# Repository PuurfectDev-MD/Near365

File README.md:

# Wacky and cute- *self claimed :)* Music Player 

**Music Player v1** is a interactive  media device (media form: music, voice recording, text, gifs and video possibly) powered by an ESP32-S3.I designed it as a personalized gift,to play unique music, affirmations,  every single day onpre-programmed schedule. v2 will have an APi endpoint to post voice recordings over the internet and other cool features. The device is a complete package for audio related projects and can be modified into other creative ideas like - (voice journal keeper, online music streaming and many more!)

---

## Features

* **Daily Present:** Automatically fetches unique content (music and text(affiramtions/notes)) from an SD card based on the current date.
* **High-quality Audio:** Uses I2S protocol with a MAX98357A DAC for clear, non-blocking WAV file playback.
* **Voice Recorder:** Record and save voice memos directly to the SD card for future playback ** Plans to stream it over the internet
* **Music Player:** Plays music playlists from the sd card
* **Peculiar Cute design** Cute 3d model case enclosure with a tounge sticking out 😛

---

##  Hardware Design

### Schematic
The system integrates an ESP32-S3 with I2S audio, SPI SD card communication, and I2C/SPI display interfacing.

### PCB Design
A custom 2-layer PCB design from kicad.

### Power Board

### 3D Model for Case
A custom 3d model case from fusion 360

---
##  Bill of Materials (BOM)

| Component           | Description                                  | Quantity |
| :------------------ | :------------------------------------------- | :------- |
| **Microcontroller** | ESP32-S3 (WROOM-1-N16R8)                     | 1        |
| **Display** | 2.4" TFT LCD (ILI9341 Driver)                | 1        |
| **Audio DAC/Amp** | MAX98357A I2S Class D Amplifier              | 1        |
| **Speaker** | 3W 4-Ohm Internal Speaker                    | 1        |
| **Rotary Encoder** | EC11 Encoder with Push-Button Switch         | 1        |
| **Touch Sensor** | TTP223 Capacitive Touch Module (Soft Power)  | 1        |
| **SD card module** | Adafruit Micro SD Card Breakout Board      | 1        |
| **Microphone** | INMP441 I2S Digital Omnidirectional Mic      | 1        |
| **RTC Module** | DS3231 High-Precision I2C RTC                | 1        |
| **Storage Card** | 16GB Micro SD Card       | 1        |
| **BMS Board** | Custom made battery management system      | 1        |
> [!NOTE]
> This is just a summary of the BOM. The complete BOM can be found in [`/BOM details/project.csv`](BOM%20details/project.csv)
---

##  Project Structure

* `firmware/pages`: Contains the class logic for each UI state (`Daily`, `Music`, `Record`, `History`).
* `main.py`: The primary async loop and state machine handler.
* `setup.py`: Hardware initialization and pin mapping.
* `master.json`: The central database for the daily gift schedule.

## File Structure:

* `/3d Model`: Contains fusion and 3d printing files for the case.
* `/firmware`: Contains the code
* `Kicad`: Kicad files (both power and main board)
       * `Power_kicad`: Custom made bms system kicad project
       * `main_kicad`: main pcb kicad project
* `/images`: For images of README.md
* `/BOM details`: For BOM from Kicad and my cost compiled for the enitre project
          *`project.csv`: For cost compiled BOM
* `Gerber Files`: For JLCPCB or any other manufacturer
          * `production_main`: Gerber for the main pcb
          * `production_power`: Gerber for the BMS pcb

---

# Why build this?
I built it becasue I really wanted to get into making a custom esp32 chip board and happened to stumble upon a music player gift idea. And from there I spiralled into making the best version of my idea. It plays a different song and displays unique affiramtions from a predefined library to bringten up someones day. OFC my handcrafted playlist library is the biggest treasure :). You can build your own too! For yourself or for someone else. Good Luck >> After you complete it, share it with me from the info at https://manishd.is-a.dev/ .

# My build

### What Works Perfectly:
* **Playback:** Successfully fetches scheduled daily gifts/affirmations and plays audio
* **Network & Time Sync:** Connects to the internet to update and synchronize time data via API
* **Custom UI:** The custom LVGL-based TFT user interface turned out beautifully and performs well 

### Improvements that could better my build:
1. **The BMS Architecture:** Looking back, splitting the power/BMS circuit onto a separate board added unnecessary assembly complexity. For v2, the power management circuit will on a singl PCB.
2. **I2S Audio Recording:** While standalone microphone test scripts work flawlessly, fully integrating the voice-recording firmware into the main async package remains a work-in-progress becasue of some pin conflict
3. **Prototyping Materials Matter:** Using standard breadboard jumper wires and low-quality solder wire made internal routing extremely messy and prone to weak joints and gave me a veryvery hard time during building. This also made the final result messy and prone to breaking down/short ciruit.
4. **Hardware Casualty:** During the final hardware assembly stages, the TFT display took some physical damage which was just devestating. But it works kinda alright so fine i guess.

<details>
<summary><b> This is the tft after damage</b></summary>
<br />
<p align="center">
  
  <br />
  <sub>It works though so its fine guess.</sub>
</p>
</details>

---
> 💡 **Note:** This video was recorded during early testing. Some UI components shown in the gallery below are not visible in the clip. use the static images for final UI reference.

#### From the outside
<table width="100%">
  <tr>
    <td width="50%" align="center">
      
      <br />
      <sub><b>Enclosure Assembly</b></sub>
    </td>
    <td width="50%" align="center">
      
      <br />
      <sub><b>Wacky Cute Tongue Profile 😛</b></sub>
    </td>
  </tr>
</table>

#### UI
<table width="100%">
  <tr>
    <td width="33%" align="center">
      
      <br />
      <sub><b>Home</b></sub>
    </td>
    <td width="33%" align="center">
      
      <br />
      <sub><b>Music Screen</b></sub>
    </td>
    <td width="33%" align="center">
      
      <br />
      <sub><b>Gift screen</b></sub>
    </td>
  </tr>
</table>

## AI USE:
I used AI heavily for the coding part. Around 40%-50%. Majority of the project is hardware based so AI use for the whole project is less than 25%. The things I used AI for - 

- Help with KICAD DRC issue
- Help with hole configuration on Fusion 360
- Troubleshooting design elements
- LVGL library and firmware setup (first time using it so thats why)
- LVGL library functions
- Acurate Encoder Input 

And a lot of debugging stuff.

*Created with love❤️.*

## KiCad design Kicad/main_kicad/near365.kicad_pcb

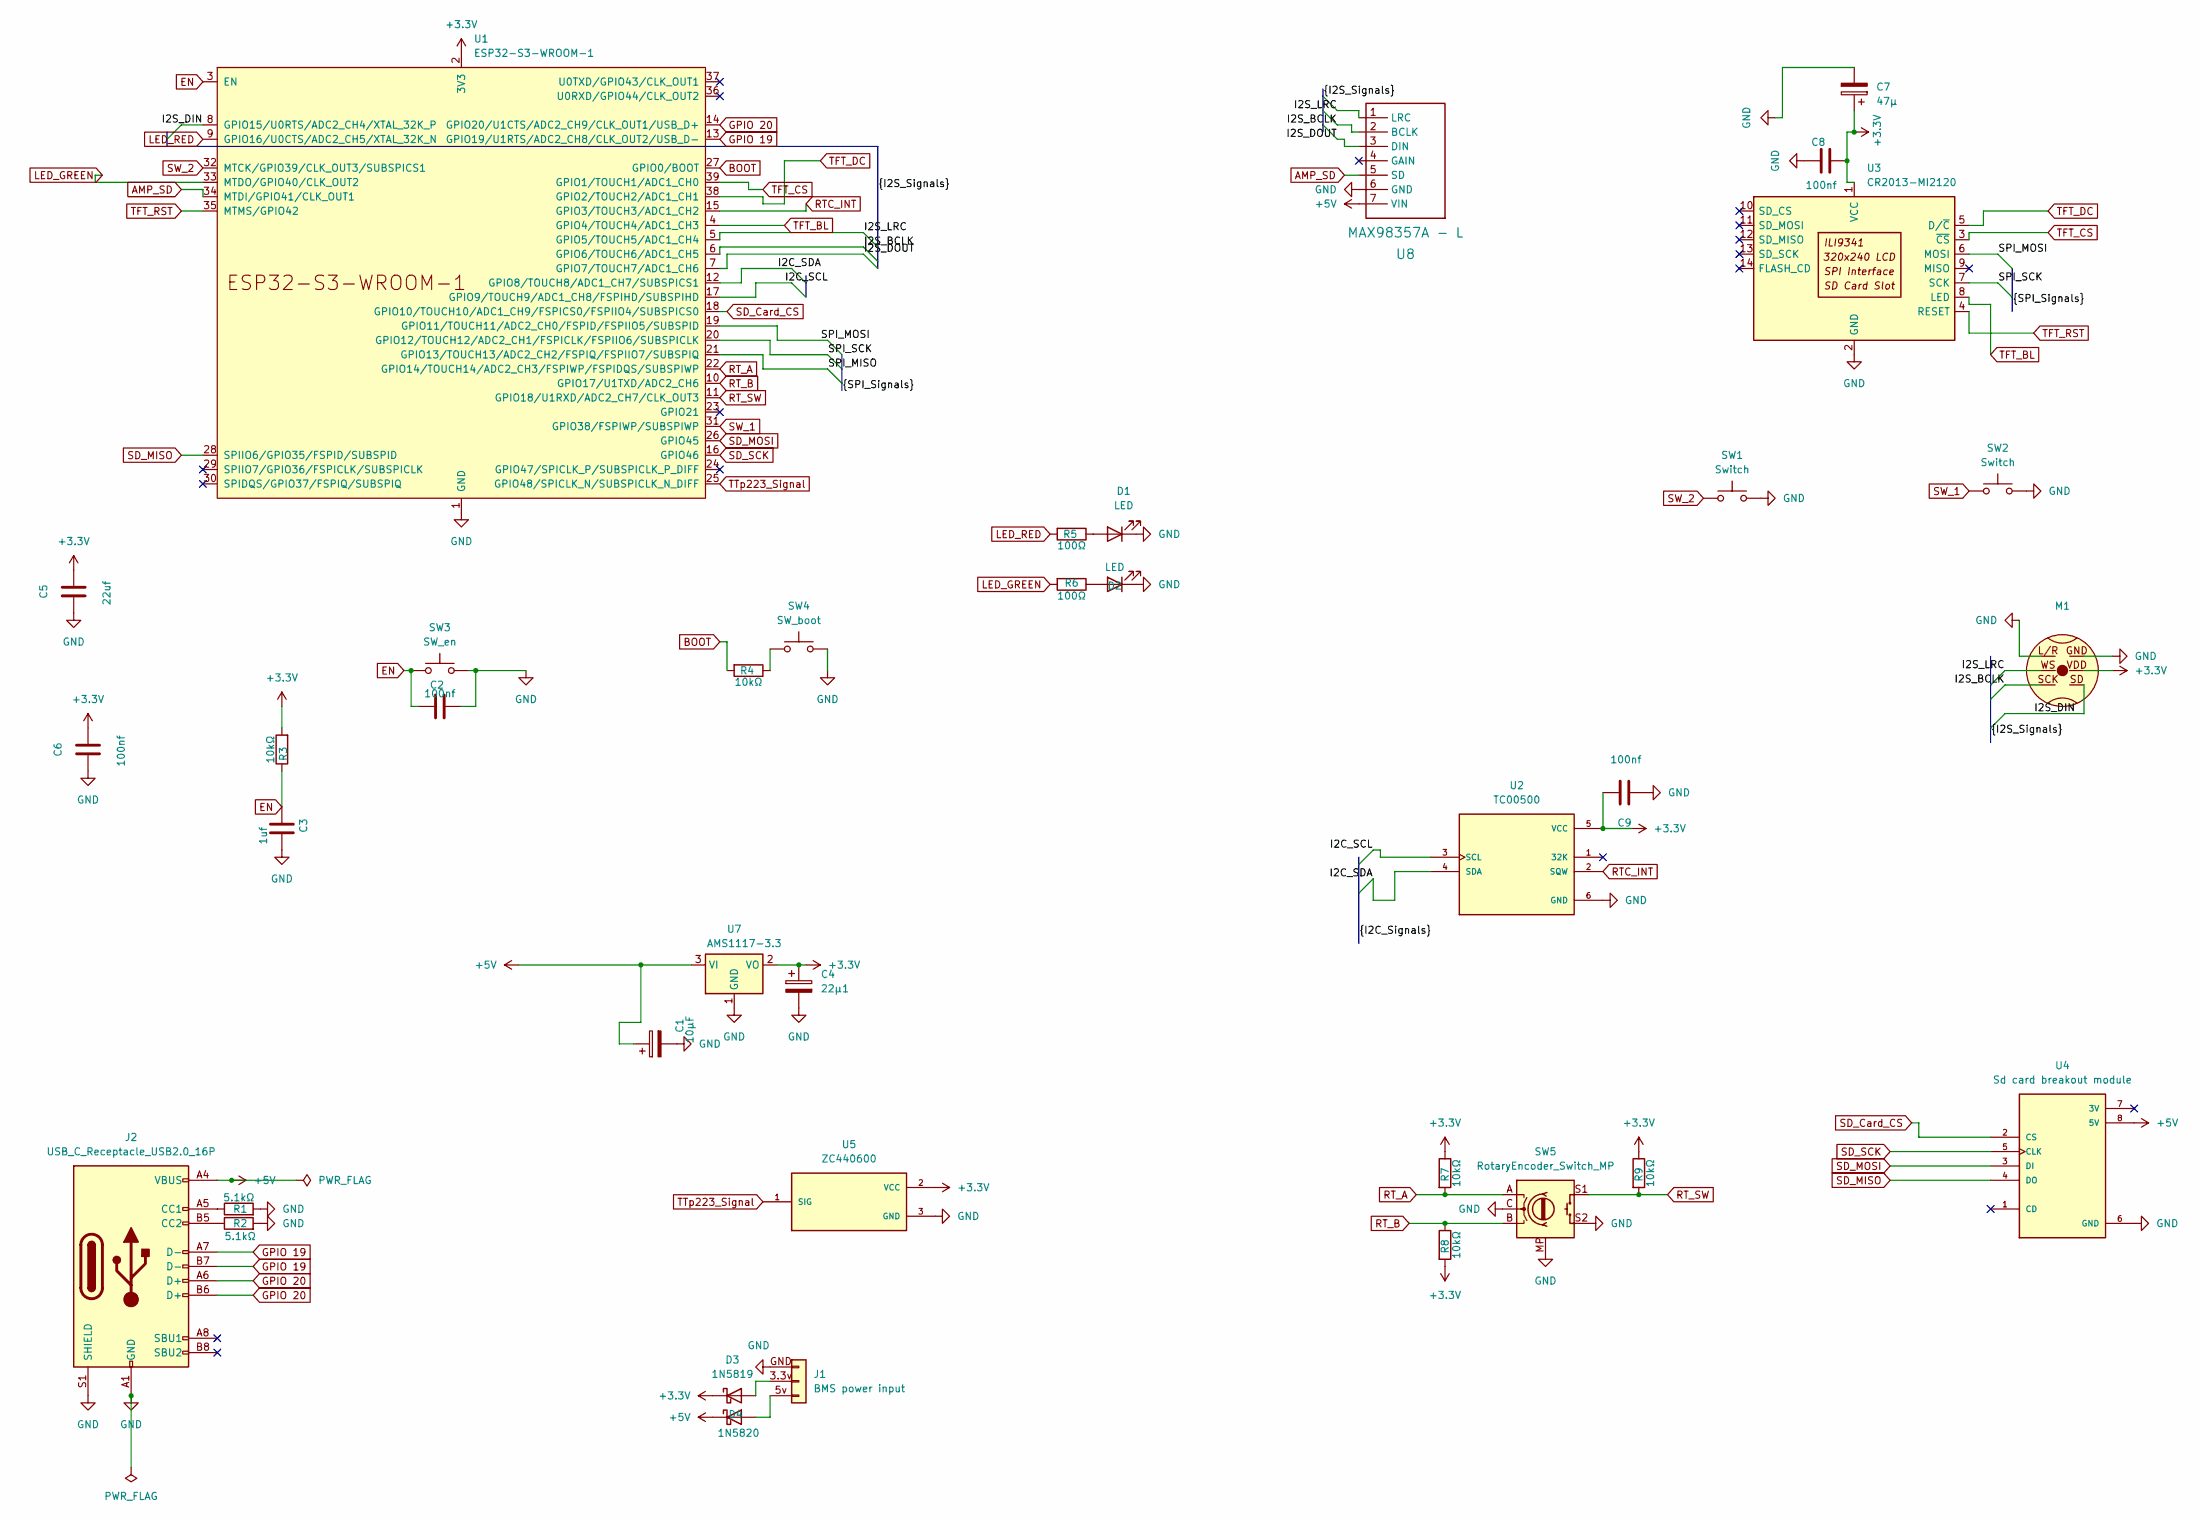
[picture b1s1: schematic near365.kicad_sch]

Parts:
C1: 10μF; CP_Radial_D5.0mm_P2.00mm
C2: 100nf; C_Disc_D3.0mm_W1.6mm_P2.50mm
C3: 1uf; C_Disc_D3.0mm_W1.6mm_P2.50mm
C4: 22μ1; CP_Radial_D5.0mm_P2.00mm
C5: 22uf; C_Disc_D5.0mm_W2.5mm_P5.00mm
C6, C8, C9: 100nf; C_Disc_D5.0mm_W2.5mm_P5.00mm
C7: 47μ; CP_Radial_D5.0mm_P2.00mm
D1, D2: LED; LED_D5.0mm
D3: 1N5819; D_DO-41_SOD81_P10.16mm_Horizontal
D4: 1N5820; D_DO-201AD_P15.24mm_Horizontal
J1: BMS power input; TerminalBlock_Phoenix_MPT-0,5-3-2.54_1x03_P2.54mm_Horizontal
J2: USB_C_Receptacle_USB2.0_16P; USB_C_Receptacle_HRO_TYPE-C-31-M-12
M1: INMP441_module
R1, R2: 5.1kΩ; R_Axial_DIN0207_L6.3mm_D2.5mm_P7.62mm_Horizontal
R3, R4, R7, R8, R9: 10kΩ; R_Axial_DIN0207_L6.3mm_D2.5mm_P7.62mm_Horizontal
R5, R6: 100Ω; R_Axial_DIN0207_L6.3mm_D2.5mm_P7.62mm_Horizontal
SW1, SW2: Switch; MX_PCB_1.00u
SW3: SW_en; SW_PUSH_6mm
SW4: SW_boot; SW_PUSH_6mm
SW5: RotaryEncoder_Switch_MP; Encoder_EC11_MX
U1: ESP32-S3-WROOM-1
U2: TC00500; MODULE_TC00500; PARTREV N/A
U3: CR2013-MI2120
U4: Sd card breakout module; MODULE_254; PARTREV Jul 31, 2013
U5: ZC440600; MODULE_ZC440600; PARTREV N/A
U7: AMS1117-3.3; SOT-223-3_TabPin2
U8: MAX98357A - L; MAX98357A_Adafruit_Breakout; Manufacturer Part 3006

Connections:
+3.3V: C4.1, C5.2, C6.2, C7.1, C8.2, C9.2, D3.1 (K), M1.VDD, R3.2, R7.1, R8.2, R9.1, U1.2 (3V3), U2.5 (VCC), U3.1 (VCC), U5.2 (VCC), U7.2 (VO)
+5V: C1.1, D4.1 (K), J2.A4 (VBUS), J2.A9 (VBUS), J2.B4 (VBUS), J2.B9 (VBUS), U4.8 (5V), U7.3 (VI), U8.7 (VIN)
/I2C_SCL: U1.17 (GPIO9/TOUCH9/ADC1_CH8/FSPIHD/SUBSPIHD), U2.3 (SCL)
/I2C_SDA: U1.12 (GPIO8/TOUCH8/ADC1_CH7/SUBSPICS1), U2.4 (SDA)
/I2S_BCLK: M1.SCK, U1.6 (GPIO6/TOUCH6/ADC1_CH5), U8.2 (BCLK)
/I2S_DIN: M1.SD, U1.8 (GPIO15/U0RTS/ADC2_CH4/XTAL_32K_P)
/I2S_DOUT: U1.7 (GPIO7/TOUCH7/ADC1_CH6), U8.3 (DIN)
/I2S_LRC: M1.WS, U1.5 (GPIO5/TOUCH5/ADC1_CH4), U8.1 (LRC)
/SPI_MISO: U1.21 (GPIO13/TOUCH13/ADC2_CH2/FSPIQ/FSPIIO7/S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)
/SPI_MOSI: U1.19 (GPIO11/TOUCH11/ADC2_CH0/FSPID/FSPIIO5/S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), U3.6 (MOSI)
/SPI_SCK: U1.20 (GPIO12/TOUCH12/ADC2_CH1/FSPICLK/FSPIIO6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), U3.7 (SCK)
AMP_SD: U1.34 (MTDI/GPIO41/CLK_OUT1), U8.5 (SD)
BOOT: R4.2, U1.27 (GPIO0/BOOT)
EN: C2.1, C3.1, R3.1, SW3.1, U1.3 (EN)
GND: C1.2, C2.2, C3.2, C4.2, C5.1, C6.1, C7.2, C8.1, C9.1, D1.1 (K), D2.1 (K), J1.GND, J2.A1 (GND), J2.A12 (GND), J2.B1 (GND), J2.B12 (GND), J2.S1 (SHIELD), M1.GND, M1.L/R, R1.2, R2.2, SW1.2, SW2.2, SW3.2, SW4.2, SW5.C, SW5.MP, SW5.S2, U1.1 (GND), U1.40 (GND), U1.41 (GND), U2.6 (GND), U3.2 (GND), U4.6 (GND), U5.3 (GND), U7.1 (GND), U8.6 (GND)
GPIO 19: J2.A7 (D-), J2.B7 (D-), U1.13 (GPIO19/U1RTS/ADC2_CH8/CLK_OUT2/USB_D-)
GPIO 20: J2.A6 (D+), J2.B6 (D+), U1.14 (GPIO20/U1CTS/ADC2_CH9/CLK_OUT1/USB_D+)
LED_GREEN: R6.2, U1.33 (MTDO/GPIO40/CLK_OUT2)
LED_RED: R5.2, U1.9 (GPIO16/U0CTS/ADC2_CH5/XTAL_32K_N)
unnamed: D1.2 (A), R5.1
unnamed: D2.2 (A), R6.1
unnamed: D3.2 (A), J1.3.3v
unnamed: D4.2 (A), J1.5v
unnamed: J2.A5 (CC1), R1.1
unnamed: J2.B5 (CC2), R2.1
unnamed: R4.1, SW4.1
RTC_INT: U1.15 (GPIO3/TOUCH3/ADC1_CH2), U2.2 (SQW)
RT_A: R7.2, SW5.A, U1.22 (GPIO14/TOUCH14/ADC2_CH3/FSPIWP/FSPIDQS/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)
RT_B: R8.1, SW5.B, U1.10 (GPIO17/U1TXD/ADC2_CH6)
RT_SW: R9.2, SW5.S1, U1.11 (GPIO18/U1RXD/ADC2_CH7/CLK_OUT3)
SD_Card_CS: U1.18 (GPIO10/TOUCH10/ADC1_CH9/FSPICS0/FSPIIO4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), U4.2 (CS)
SD_MISO: U1.28 (SPIIO6/GPIO35/FSPID/SUBSPID), U4.4 (DO)
SD_MOSI: U1.26 (GPIO45), U4.3 (DI)
SD_SCK: U1.16 (GPIO46), U4.5 (CLK)
SW_1: SW2.1, U1.31 (GPIO38/FSPIWP/SUBSPIWP)
SW_2: SW1.1, U1.32 (MTCK/GPIO39/CLK_OUT3/SUBSPICS1)
TFT_BL: U1.4 (GPIO4/TOUCH4/ADC1_CH3), U3.8 (LED)
TFT_CS: U1.39 (GPIO1/TOUCH1/ADC1_CH0), U3.3 (~CS)
TFT_DC: U1.38 (GPIO2/TOUCH2/ADC1_CH1), U3.5 (D/~C)
TFT_RST: U1.35 (MTMS/GPIO42), U3.4 (RESET)
TTp223_Signal: U1.25 (GPIO48/SPICLK_N/SUBSPICLK_N_DIFF), U5.1 (SIG)

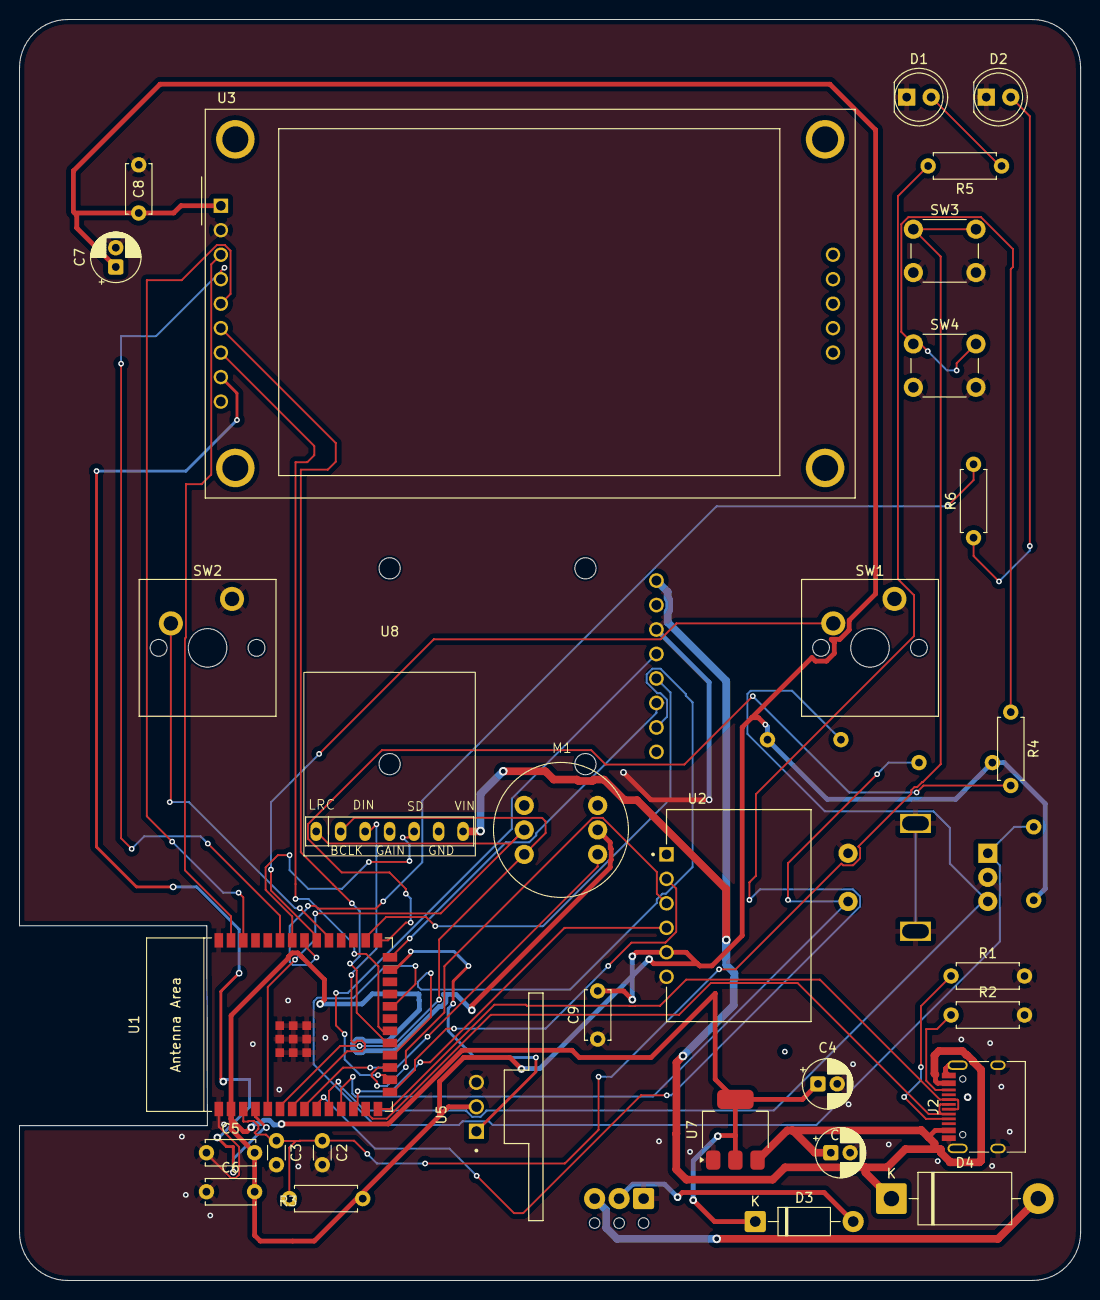
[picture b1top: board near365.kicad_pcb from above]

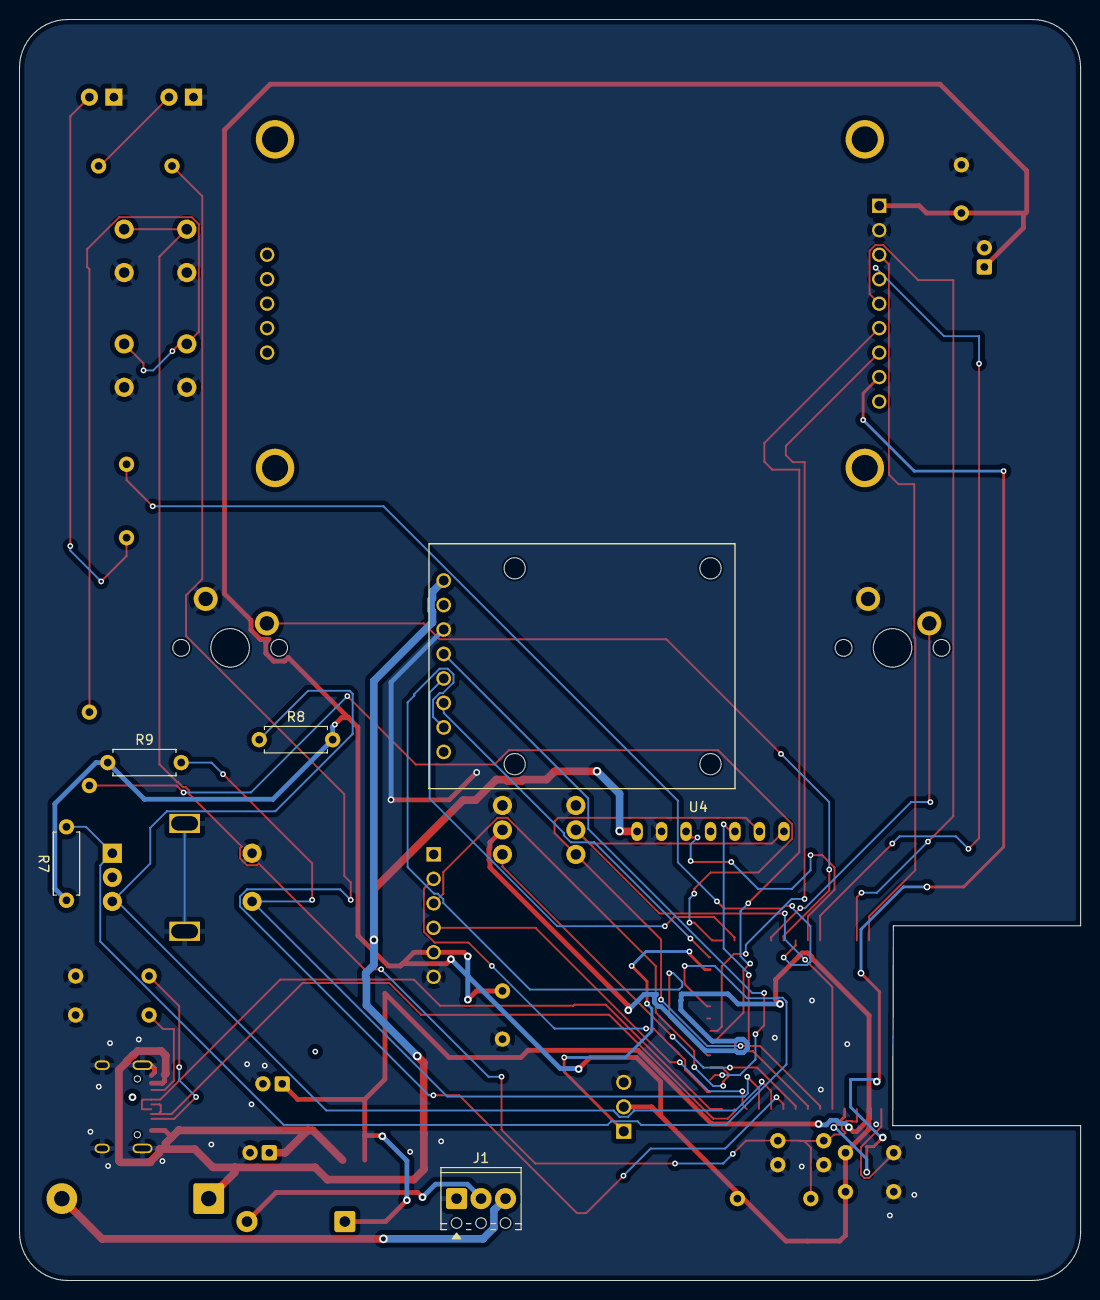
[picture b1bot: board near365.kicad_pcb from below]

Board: 2 copper layers, 110.1 x 130.8 mm, 37 parts (6 on the bottom side), 40 nets.

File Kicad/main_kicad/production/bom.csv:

Designator,Footprint,Quantity,Value,LCSC Part #
C1,CP_Radial_D5.0mm_P2.00mm,1,10μF,
C2,C_Disc_D3.0mm_W1.6mm_P2.50mm,1,100nf,
C3,C_Disc_D3.0mm_W1.6mm_P2.50mm,1,1uf,
C4,CP_Radial_D5.0mm_P2.00mm,1,22μ1,
C5,C_Disc_D5.0mm_W2.5mm_P5.00mm,1,22uf,
"C6, C8, C9",C_Disc_D5.0mm_W2.5mm_P5.00mm,3,100nf,
C7,CP_Radial_D5.0mm_P2.00mm,1,47μ,
"D1, D2",LED_D5.0mm,2,LED,
D3,D_DO-41_SOD81_P10.16mm_Horizontal,1,1N5819,
D4,D_DO-201AD_P15.24mm_Horizontal,1,1N5820,
J1,"TerminalBlock_Phoenix_MPT-0,5-3-2.54_1x03_P2.54mm_Horizontal",1,BMS power input,
J2,USB_C_Receptacle_HRO_TYPE-C-31-M-12,1,USB_C_Receptacle_USB2.0_16P,
M1,INMP441_module,1,~,
"R1, R2",R_Axial_DIN0207_L6.3mm_D2.5mm_P7.62mm_Horizontal,2,5.1kΩ,
"R3, R4, R7, R8, R9",R_Axial_DIN0207_L6.3mm_D2.5mm_P7.62mm_Horizontal,5,10kΩ,
"R5, R6",R_Axial_DIN0207_L6.3mm_D2.5mm_P7.62mm_Horizontal,2,100Ω,
"SW1, SW2",MX_PCB_1.00u,2,Switch,
SW3,SW_PUSH_6mm,1,SW_en,
SW4,SW_PUSH_6mm,1,SW_boot,
SW5,Encoder_EC11_MX,1,RotaryEncoder_Switch_MP,
U1,ESP32-S3-WROOM-1,1,ESP32-S3-WROOM-1,
U2,MODULE_TC00500,1,TC00500,
U3,CR2013-MI2120,1,CR2013-MI2120,
U4,MODULE_254,1,Sd card breakout module,
U5,MODULE_ZC440600,1,ZC440600,
U7,SOT-223-3_TabPin2,1,AMS1117-3.3,
U8,MAX98357A_Adafruit_Breakout,1,MAX98357A - L,

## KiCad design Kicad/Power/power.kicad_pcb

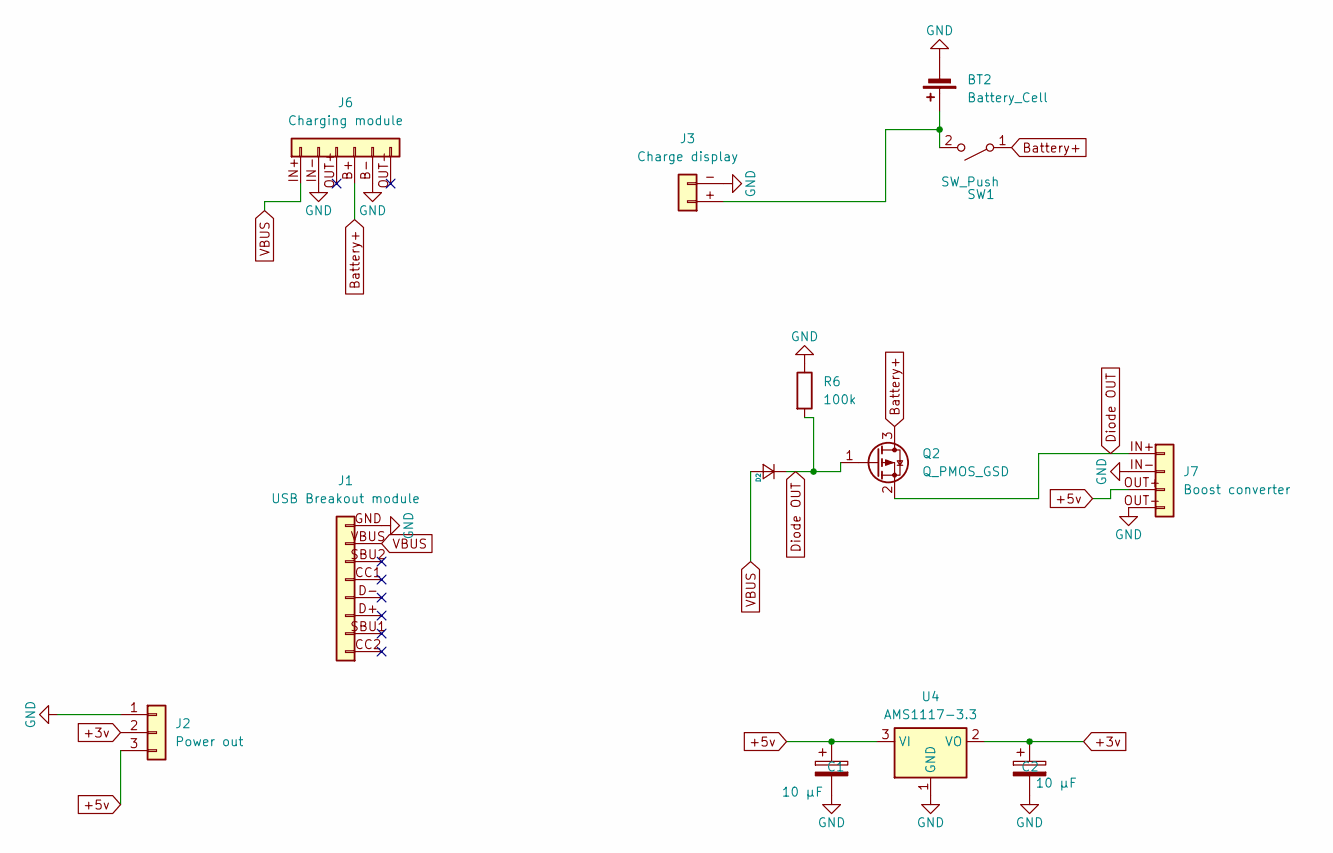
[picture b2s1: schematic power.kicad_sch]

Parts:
BT2: Battery_Cell; TerminalBlock_Phoenix_PT-1,5-2-3.5-H_1x02_P3.50mm_Horizontal
C1, C2: 10 µF; CP_Radial_Tantal_D4.5mm_P2.50mm
D2: Diode_DO-35
J1: USB Breakout module; Usb_breakout board
J2: Power out; TerminalBlock_Phoenix_MPT-0,5-3-2.54_1x03_P2.54mm_Horizontal
J3: Charge display; charge_display
J6: Charging module; TP4056-Module
J7: Boost converter; Boost_converter_3A
Q2: Q_PMOS_GSD; TO-220-3_Vertical
R6: 100k; R_Axial_DIN0204_L3.6mm_D1.6mm_P5.08mm_Horizontal
SW1: SW_Push; Switch_pads
U4: AMS1117-3.3; SOT-223-3_TabPin2

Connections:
+3v: C2.1, J2.2 (3.3v), U4.2 (VO)
+5v: C1.1, J2.3 (5v), J7.OUT+, U4.3 (VI)
Battery+: J6.B+, Q2.3 (D), SW1.1 (A)
Diode OUT: D2.1 (K), J7.IN+, Q2.1 (G), Q2.2 (S), R6.2
GND: BT2.2 (-), C1.2, C2.2, J1.GND, J2.1 (GND), J3.-, J6.B-, J6.IN-, J7.IN-, J7.OUT-, R6.1, U4.1 (GND)
unnamed: BT2.1 (+), J3.+, SW1.2 (B)
VBUS: D2.2 (A), J1.VBUS, J6.IN+

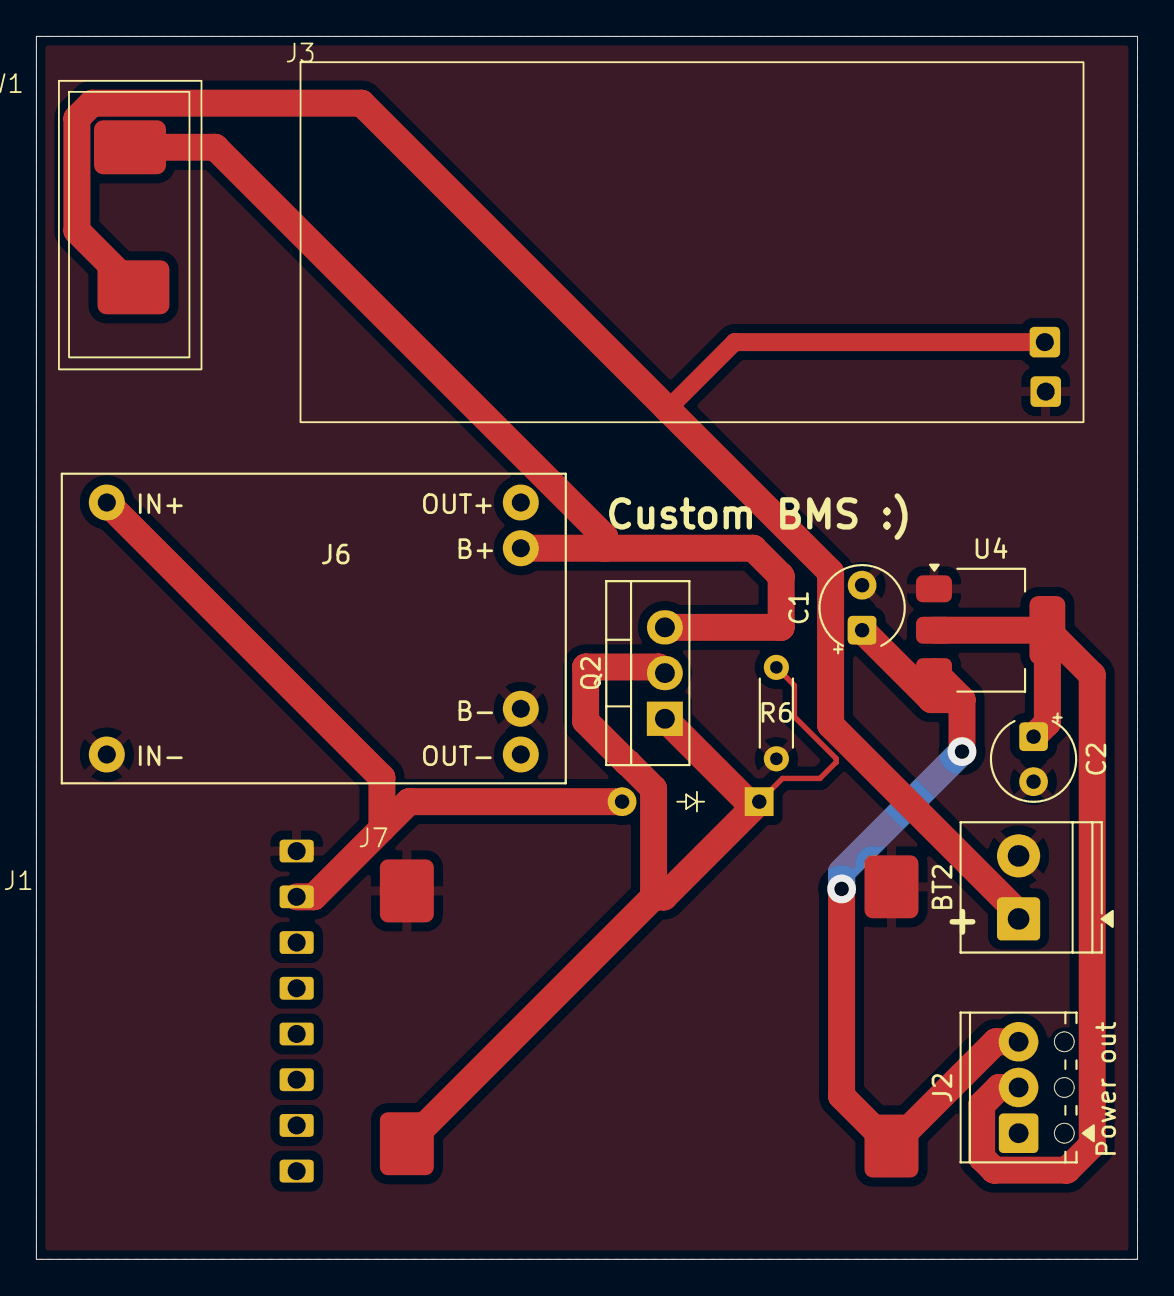
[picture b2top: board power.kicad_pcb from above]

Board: 2 copper layers, 61.2 x 67.9 mm, 13 parts (0 on the bottom side), 7 nets.

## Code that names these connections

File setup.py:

import ili9341
from ili9341 import Display
from ds3231 import DS3231
from machine import I2S
import time
master_file = master.json #file on sd card with all info   - stored on sd card
daily_file = daily.json #file info extracted on this for today (one day) -stored on esp flash



WIFI_SSID = ""
WIFI_PASS = ""


SPI_MOSI = 11
SPI_MISO = 13
SPI_SCK = 12

I2C_SDA = 8
I2C_SCL = 9

SD_CS= 10
SD_MOSI = 46
SD_MISO = 35
SD_SCK =45

TFT_CS = 1
TFT_DC =2
TFT_RST= 42
TFT_BL = 4


I2S_DOUT = 7
I2S_BCLK =6
I2S_LRC =5
I2C_DIN =15
AMP_SD =41


button1 = 38
button2 = 39
RT_SW = 18
RT_A =14
RT_B = 17

## font_Unispace = XglcdFont('Unispace12x24.c', 12, 24)   - I can import fonts like this Ill test this when I get the display


class System_Init:
    def __init__(self):
        self.sd_mounted = False
        self.i2s_initialized = False
        self.rtc_initialized = False
        self.display_initialized = False
        self.spi_initialized= False

        self.spi_tft = None
        self.spi_sd = None
        self.i2s = None

        self.display = None
        self.sd_card = None
        self.rtc = None
       

        #display configuartion
        self.display_width = 320
        self.display_height = 240
        self.display_rotation = 270
        
    def init_spi(self):
        print("Initializing SPI")

        try:
            self.spi_tft = SPI(2, baudrate=10000000, sck=Pin(SPI_SCK), mosi=Pin(SPI_MOSI), miso=Pin(SPI_MISO))
            self.spi_sd= SPI(1, baudrate=10000000,sck= SD_SCK, mosi = Pin(SD_MOSI), miso = Pin(SD_MISO))
            
            self.spi_initialized = True
            return True
        
        except Exception as e:
            print(f"Init failed {e}")
            self.spi_initialized =False
            return False
        

    def init_i2c_clock(self):
        print("Initializing I2c")

        try:
            i2c = I2C(0, scl=Pin(I2C_SCL), sda=Pin(I2C_SDA), freq=400000)
            self.rtc = DS3231(i2c)
            print("I2c Clock Initalized")
            self.rtc_initialized= True

            # Scan for I2C devices
            devices = self.i2c.scan()
            print(f"Found {len(devices)} I2C device(s): {[hex(addr) for addr in devices]}")
        except Exception as e:
            print(f"Clock init failed {e}")
            self.rtc_initialized= False


    def init_display(self):
        print("Display init")
        try:
            self.display = Display(self.spi_tft,cs=Pin(TFT_CS),dc=Pin(TFT_DC),rst=Pin(TFT_RST),width=self.display_width,height=self.display_height,rotation=self.display_rotation) 

            # Set Backlight pin High
            Pin(TFT_BL, Pin.OUT).value(1)
            self.display.clear()
            self.display_initialized = True

            display.draw_text(100,50,"Display Init Success",0x001F) #drawing text for confirmation -will remove after testing
            
            return True
        except Exception as e:
            print(f"Display initialization failed: {e}")
            self.display_initialized = False
            return False
        

    def init_sdcard(self):
        print("Sd inititialization")

        try:
            self.sd_card = SDCard(self.spi_sd, cs=Pin(SD_CS),freq=20000000 )

            #have to check which freq it can run at later
            os.mount(self.sd_card, "/sd")
            print(files)    #for testing only
            print("Sucess")
            self.sd_mounted =True
            return True

        except Exception as e:
            print(f"Failure {e}")
            self.sd_mounted=  False

    def init_i2s(self):
        print("Initializing I2S")
        
        try:
            self.amp_en = Pin(AMP_SD, Pin.OUT)  #keeping this as output to control amp on/off
            self.amp_en.value(1) #high


            self.i2s = I2S(0, 
                           sck=Pin(I2S_BCLK), 
                           ws=Pin(I2S_LRC), 
                           sd=Pin(I2S_DOUT),
                           mode=I2S.TX, 
                           bits=16, 
                           format=I2S.MONO, 
                           rate=16000, 
                           ibuf=20000)
            
            self.i2s_initialized = True
            print("I2S initialized")
            return True
            
        except Exception as e:
            print(f"I2S failed {e}")
            self.i2s_initialized = False
            return False
            
    def run_all(self): #boot sequence
        self.init_spi()
        self.init_i2c_clock()
        self.init_display()
        self.init_sdcard()
        self.init_i2s()

class Controls():
    def __init__(self):
        self.btn1 = Pin(button1, Pin.IN, Pin.PULL_UP)
        self.btn2 = Pin(button2, Pin.IN, Pin.PULL_UP)

        self.pin_a = Pin(RT_A, Pin.IN, Pin.PULL_UP)
        self.pin_b = Pin(RT_B, Pin.IN, Pin.PULL_UP)
        self.pin_sw = Pin(RT_SW, Pin.IN, Pin.PULL_UP)
        
        self.encoder_value = 1
        self.last_val_a = self.pin_a.value()
        print("Encoder pins configured")

    def read_encoder(self):
        current_val_a = self.pin_a.value()
        change_detected = False
        
        if current_val_a != self.last_val_a:
            # Determine direction
            if self.pin_b.value() != current_val_a:
                self.encoder_value += 1  # Clockwise
            else:
                self.encoder_value -= 1  # Counter-clockwise
            
         
            self.last_val_a = current_val_a
            change_detected = True
            
        return change_detected
    
    def button_pressed(self):
        if pin_Sw.value() == 0:
            return True
        return False

    def map_encoder_values(self, maxlimit):
        # This one line handles both the upper and lower bounds
        self.encoder_value = max(1, min(maxlimit, self.encoder_value))
        return self.encoder_value

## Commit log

2026-01-26 Full project (v1) commit
2026-03-06 New changes- new case redesign
2026-03-06 Readme Update
2026-03-08 FINAL readme update
2026-03-09 Added BOM info
2026-03-09 README edit
2026-03-20 Updated power, made changes to 3d front plate, added pull down r to encoder
2026-06-02 LVGL and display with ui pages switching on button presses. Speaker setup
2026-06-11 Music playback and music list on page
2026-06-12 Music selection to play any song and encoder input fix
2026-06-12 Wifi connection, time fetch and Present page working *without audio
2026-06-13 Added song page and logic. Bug fixes
2026-06-13 Song page logic with prev and next. UI for song page. Ui fixes. Bug fixes
2026-06-14 Home page completion and bug fixes
2026-06-30 Finishing up
